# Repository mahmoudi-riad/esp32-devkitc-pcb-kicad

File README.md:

# esp32-devkitc-pcb-kicad
 I designed ESP32 dev kit (ESP32-WROOM module) with kciad . I keep it like the real ESP32 boards mesurment so it can fit on a breadboard and other stuff

 just download all the files and put them in a foulder and open it with kicad , you find there shymatics and pcb
Line above<br>
<br>

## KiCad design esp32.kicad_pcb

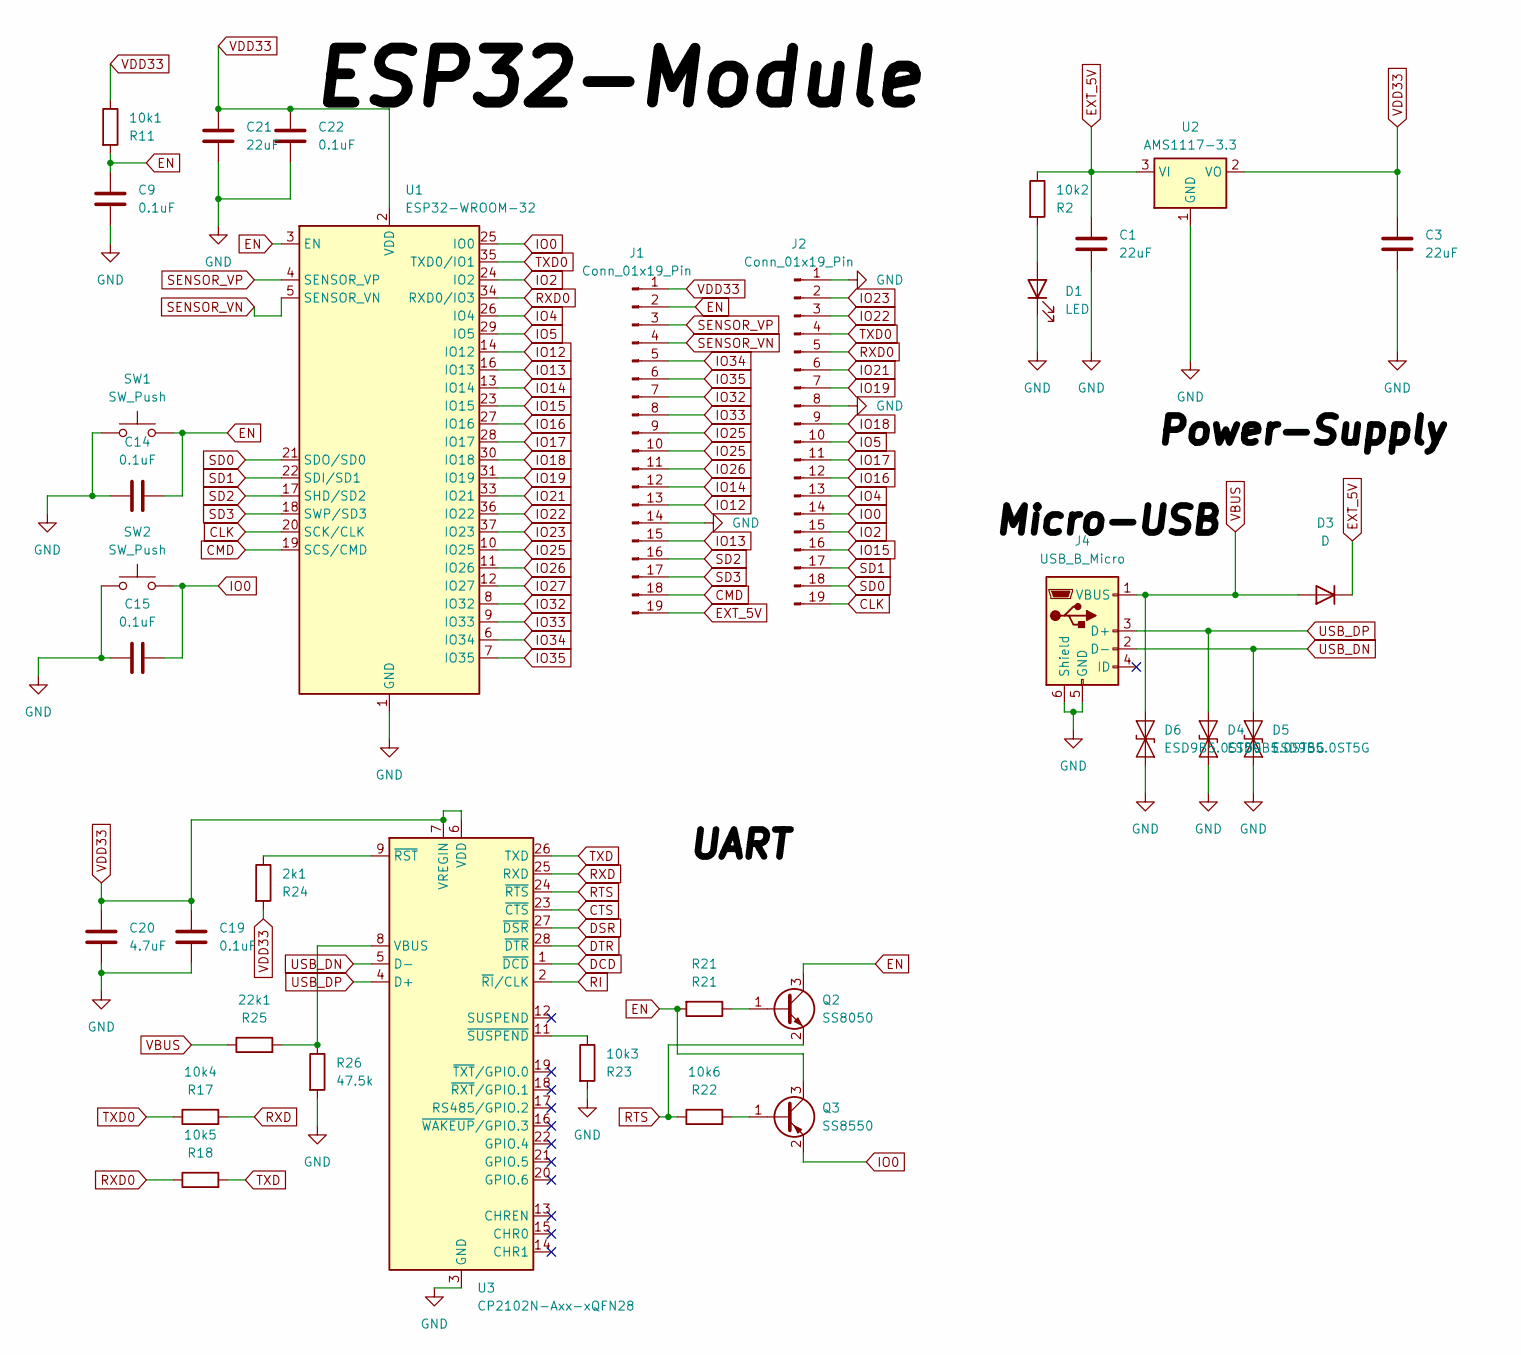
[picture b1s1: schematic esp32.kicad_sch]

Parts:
2k1: R24; R_0402_1005Metric
10k1: R11; R_0402_1005Metric
10k2: R2; R_0402_1005Metric
10k3: R23; R_0402_1005Metric
10k4: R17; R_0402_1005Metric
10k5: R18; R_0402_1005Metric
10k6: R22; R_0402_1005Metric
22k1: R25; R_0402_1005Metric
C1, C3, C21: 22uF; C_0402_1005Metric
C9, C14, C15, C19, C22: 0.1uF; C_0402_1005Metric
C20: 4.7uF; C_0402_1005Metric
D1: LED; LED_0402_1005Metric
D3: D; D_0805_2012Metric
D4, D5, D6: ESD9B5.0ST5G; D_SOD-923
J1, J2: Conn_01x19_Pin; PinHeader_1x19_P2.54mm_Vertical
J4: USB_B_Micro; USB_Micro-B_Molex_47346-0001
Q2: SS8050; SOT-23
Q3: SS8550; SOT-23
R21: R21; R_0402_1005Metric
R26: 47.5k; R_0402_1005Metric
SW1, SW2: SW_Push; SW_SPST_CK_RS282G05A3
U1: ESP32-WROOM-32; ESP32-WROOM-32E
U2: AMS1117-3.3; SOT-223-3_TabPin2
U3: CP2102N-Axx-xQFN28; QFN-28-1EP_5x5mm_P0.5mm_EP3.35x3.35mm

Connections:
CLK: J2.19, U1.20 (SCK/CLK)
CMD: J1.18, U1.19 (SCS/CMD)
CTS: U3.23 (~CTS)
DCD: U3.1 (~DCD)
DSR: U3.27 (~DSR)
DTR: U3.28 (~DTR)
EN: 10k1.2, C9.1, C14.1, J1.2, Q2.3 (C), Q3.3 (C), R21.2, SW1.2, U1.3 (EN)
EXT_5V: 10k2.1, C1.2, D3.1 (K), J1.19, U2.3 (VI)
GND: 10k3.2, C1.1, C3.1, C9.2, C14.2, C15.2, C19.2, C20.2, C21.2, C22.2, D1.1 (K), D4.1 (A1), D5.1 (A1), D6.1 (A1), J1.14, J2.1, J2.8, J4.5 (GND), J4.6 (Shield), R26.2, SW1.1, SW2.1, U1.1 (GND), U1.15 (GND), U1.38 (GND), U1.39 (GND), U2.1 (GND), U3.3 (GND), U3.29 (GND)
IO0: C15.1, J2.14, Q3.2 (E), SW2.2, U1.25 (IO0)
IO2: J2.15, U1.24 (IO2)
IO4: J2.13, U1.26 (IO4)
IO5: J2.10, U1.29 (IO5)
IO12: J1.13, U1.14 (IO12)
IO13: J1.15, U1.16 (IO13)
IO14: J1.12, U1.13 (IO14)
IO15: J2.16, U1.23 (IO15)
IO16: J2.12, U1.27 (IO16)
IO17: J2.11, U1.28 (IO17)
IO18: J2.9, U1.30 (IO18)
IO19: J2.7, U1.31 (IO19)
IO21: J2.6, U1.33 (IO21)
IO22: J2.3, U1.36 (IO22)
IO23: J2.2, U1.37 (IO23)
IO25: J1.9, J1.10, U1.10 (IO25)
IO26: J1.11, U1.11 (IO26)
IO27: U1.12 (IO27)
IO32: J1.7, U1.8 (IO32)
IO33: J1.8, U1.9 (IO33)
IO34: J1.5, U1.6 (IO34)
IO35: J1.6, U1.7 (IO35)
unnamed: 10k2.2, D1.2 (A)
unnamed: Q2.1 (B), R21.1
unnamed: 10k6.2, Q3.1 (B)
unnamed: 22k1.2, R26.1, U3.8 (VBUS)
unnamed: 2k1.1, U3.9 (~RST)
unnamed: 10k3.1, U3.11 (~SUSPEND)
RI: U3.2 (~RI/CLK)
RTS: 10k6.1, Q2.2 (E), U3.24 (~RTS)
RXD: 10k4.2, U3.25 (RXD)
RXD0: 10k5.1, J2.5, U1.34 (RXD0/IO3)
SD0: J2.18, U1.21 (SDO/SD0)
SD1: J2.17, U1.22 (SDI/SD1)
SD2: J1.16, U1.17 (SHD/SD2)
SD3: J1.17, U1.18 (SWP/SD3)
SENSOR_VN: J1.4, U1.5 (SENSOR_VN)
SENSOR_VP: J1.3, U1.4 (SENSOR_VP)
TXD: 10k5.2, U3.26 (TXD)
TXD0: 10k4.1, J2.4, U1.35 (TXD0/IO1)
USB_DN: D5.2 (A2), J4.2 (D-), U3.5 (D-)
USB_DP: D4.2 (A2), J4.3 (D+), U3.4 (D+)
VBUS: 22k1.1, D3.2 (A), D6.2 (A2), J4.1 (VBUS)
VDD33: 2k1.2, 10k1.1, C3.2, C19.1, C20.1, C21.1, C22.1, J1.1, U1.2 (VDD), U2.2 (VO), U3.6 (VDD), U3.7 (VREGIN)

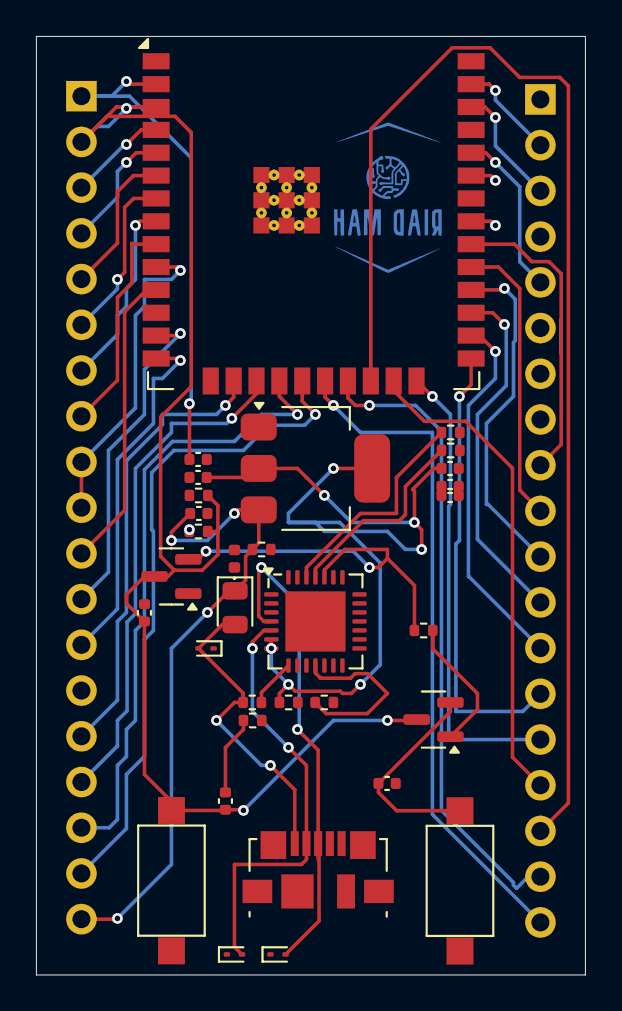
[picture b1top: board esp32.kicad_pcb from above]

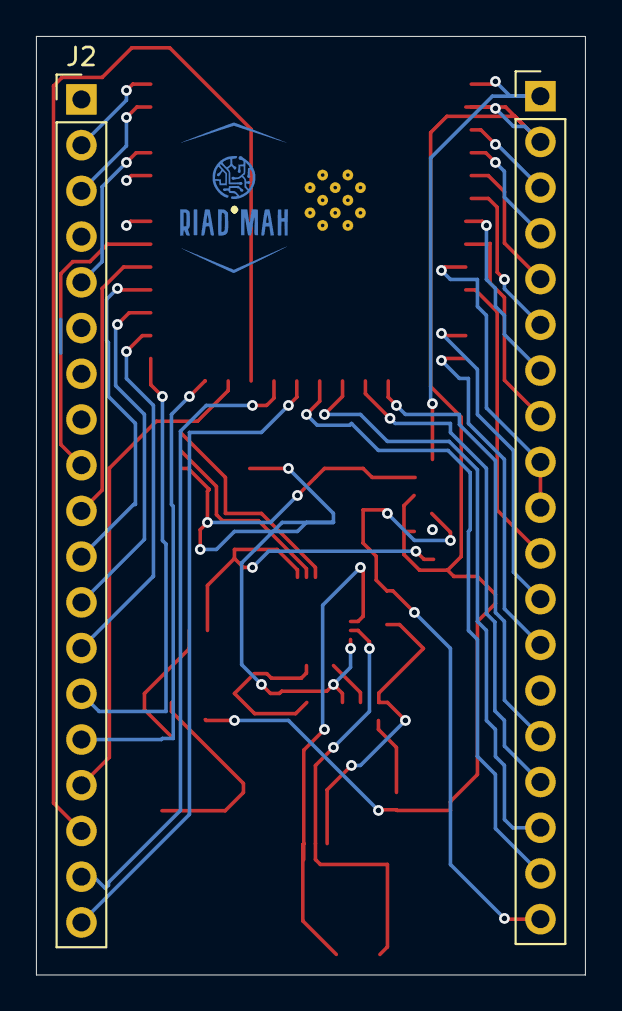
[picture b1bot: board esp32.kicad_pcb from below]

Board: 2 copper layers, 30.5 x 52.1 mm, 35 parts (3 on the bottom side), 47 nets.

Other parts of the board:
.: LOGO; riadLogo10mmriad
